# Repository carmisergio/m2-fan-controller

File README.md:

# M.2 fan controller
A simple PWM fan controller designed to fit in an E-Key M.2 slot normally designed for WiFi/Bluetooth cards.

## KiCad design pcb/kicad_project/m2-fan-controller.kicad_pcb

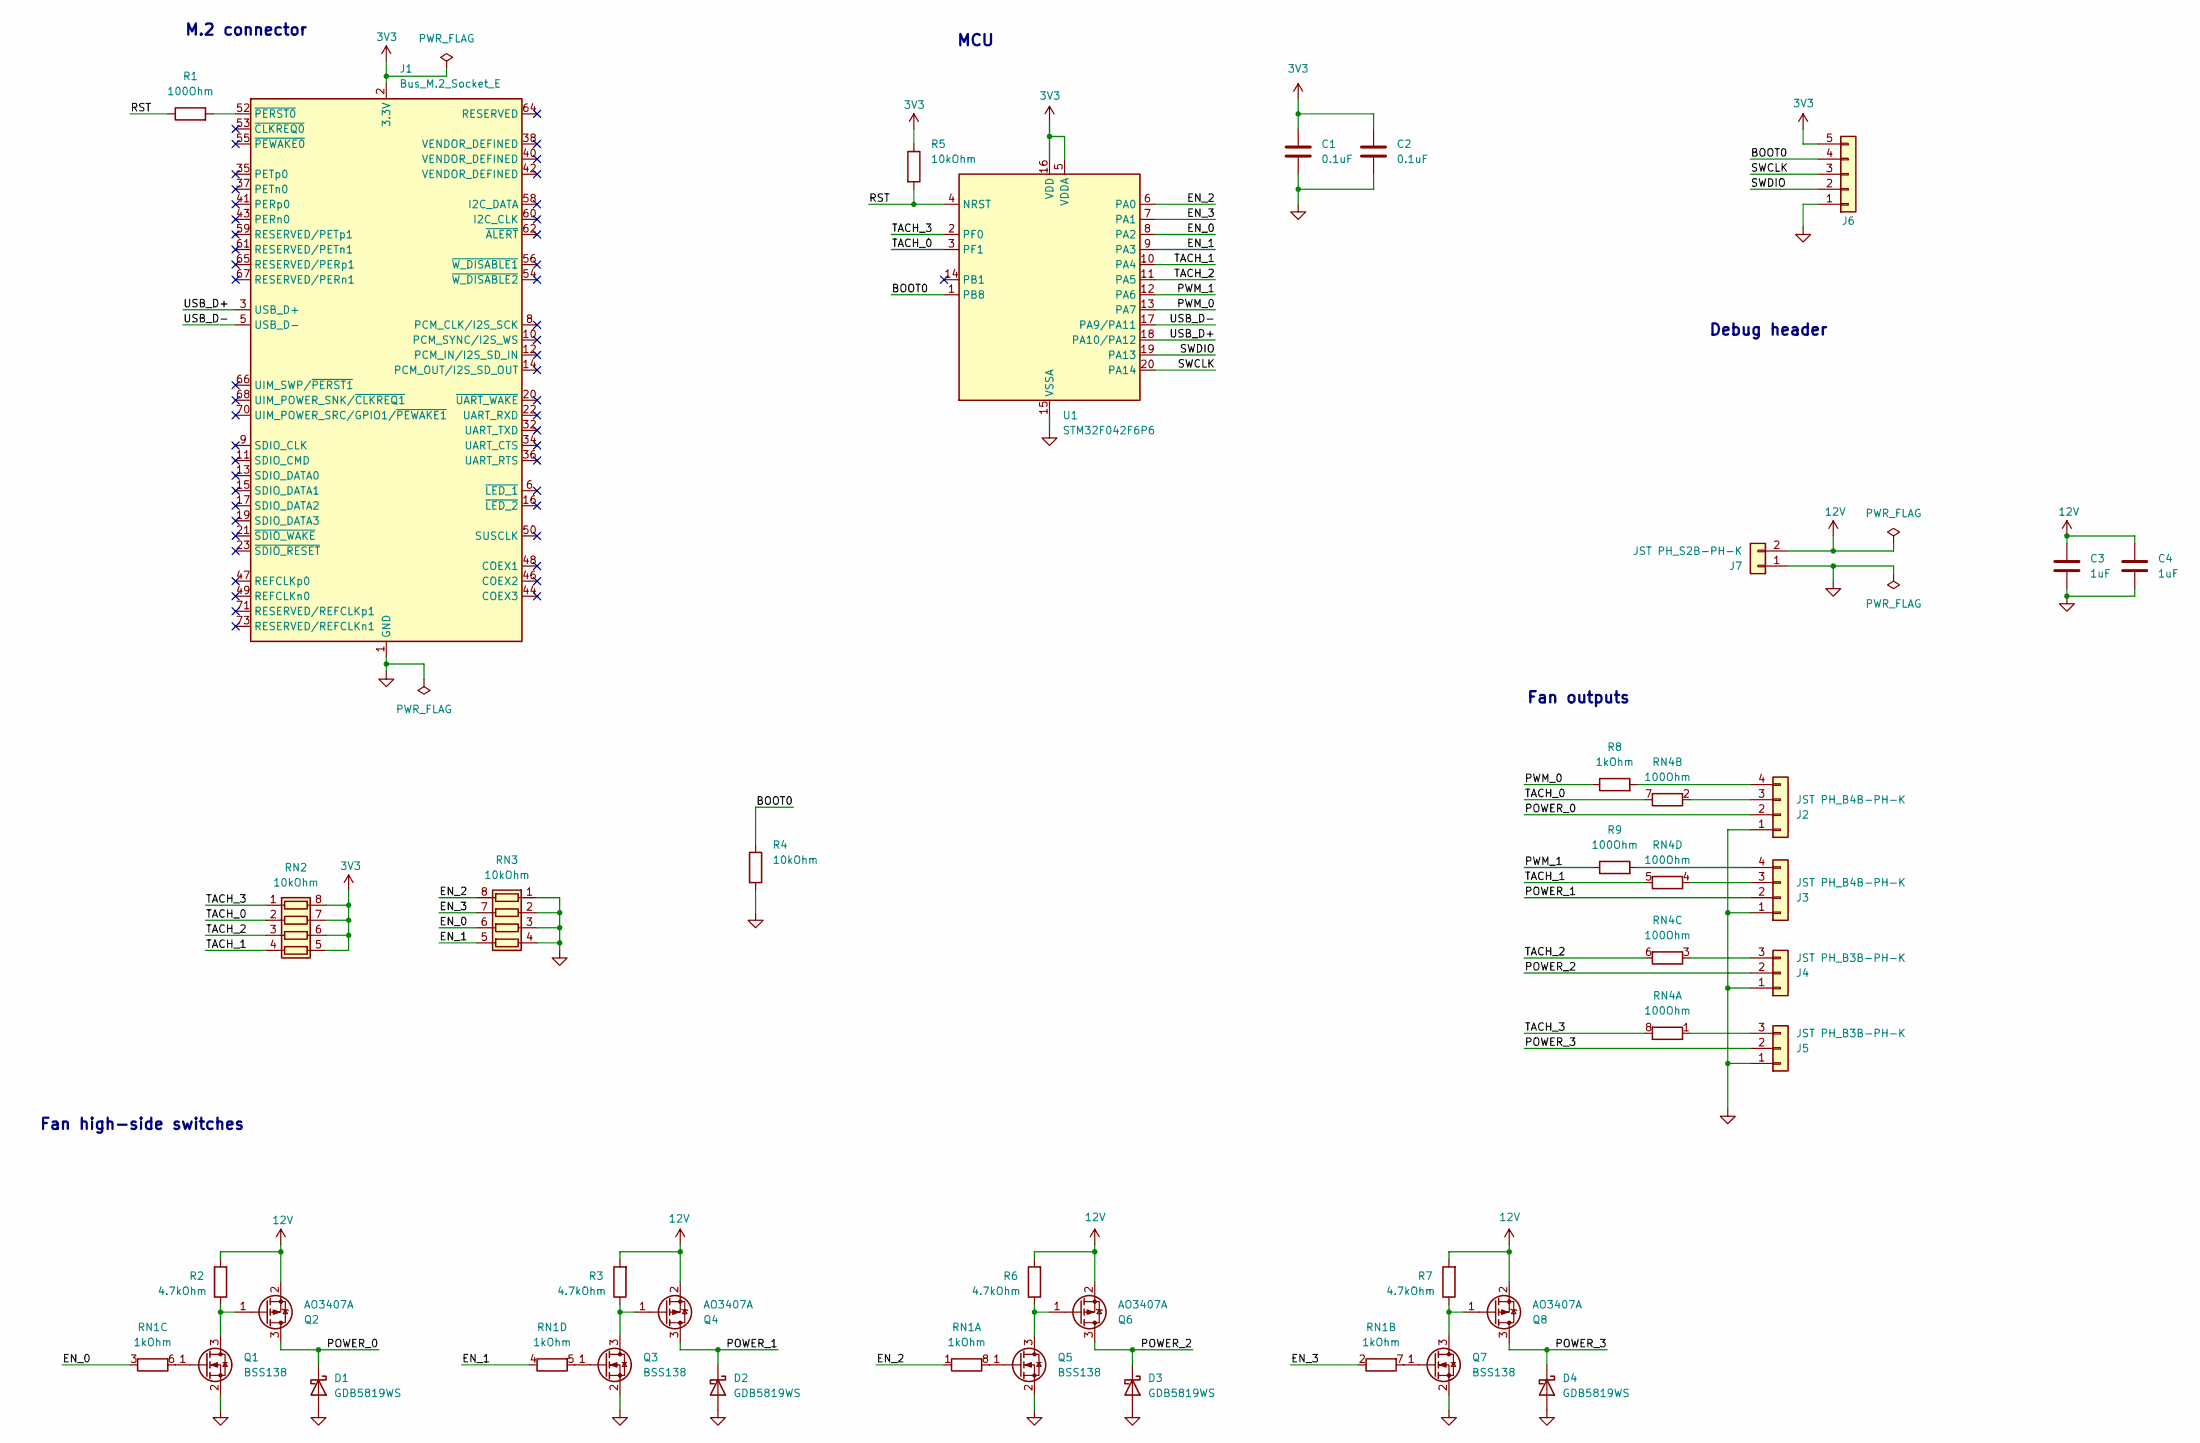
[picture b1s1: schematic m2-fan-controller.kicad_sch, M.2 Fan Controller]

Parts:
C1, C2: 0.1uF; C_0603_1608Metric_Pad1.08x0.95mm_HandSolder
C3, C4: 1uF; C_0805_2012Metric_Pad1.18x1.45mm_HandSolder
D1, D2, D3, D4: GDB5819WS; D_SOD-323_HandSoldering
J1: Bus_M.2_Socket_E; M.2_2230-xx-E
J2, J3: JST PH_B4B-PH-K; JST_PH_B4B-PH-K_1x04_P2.00mm_Vertical
J4, J5: JST PH_B3B-PH-K; JST_PH_B3B-PH-K_1x03_P2.00mm_Vertical
J6: Conn_02x02_Odd_Even; PinHeader_1x05_P1.27mm_Vertical
J7: JST PH_S2B-PH-K; JST_PH_B2B-PH-K_1x02_P2.00mm_Vertical
Q1, Q3, Q5, Q7: BSS138; SOT-23
Q2, Q4, Q6, Q8: AO3407A; SOT-23
R1, R9: 100Ohm; R_0603_1608Metric_Pad0.98x0.95mm_HandSolder
R2, R3, R6, R7: 4.7kOhm; R_0603_1608Metric_Pad0.98x0.95mm_HandSolder
R4, R5: 10kOhm; R_0603_1608Metric_Pad0.98x0.95mm_HandSolder
R8: 1kOhm; R_0603_1608Metric_Pad0.98x0.95mm_HandSolder
RN1: 1kOhm; R_Array_Convex_4x0603
RN2, RN3: 10kOhm; R_Array_Convex_4x0603
RN4: 100Ohm; R_Array_Convex_4x0603
U1: STM32F042F6P6; TSSOP-20_4.4x6.5mm_P0.65mm

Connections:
3V3: C1.1, C2.1, J1.2 (3.3V), J1.4 (3.3V), J1.72 (3.3V), J1.74 (3.3V), J6.5, R5.1, RN2.5 (R4.2), RN2.6 (R3.2), RN2.7 (R2.2), RN2.8 (R1.2), U1.5 (VDDA), U1.16 (VDD)
12V: C3.1, C4.1, J7.2, Q2.2 (S), Q4.2 (S), Q6.2 (S), Q8.2 (S), R2.2, R3.2, R6.2, R7.2
/BOOT0: J6.4, R4.1, U1.1 (PB8)
/EN_0: RN1.3 (R3.1), RN3.6 (R3.2), U1.8 (PA2)
/EN_1: RN1.4 (R4.1), RN3.5 (R4.2), U1.9 (PA3)
/EN_2: RN1.1 (R1.1), RN3.8 (R1.2), U1.6 (PA0)
/EN_3: RN1.2 (R2.1), RN3.7 (R2.2), U1.7 (PA1)
/POWER_0: D1.1 (K), J2.2, Q2.3 (D)
/POWER_1: D2.1 (K), J3.2, Q4.3 (D)
/POWER_2: D3.1 (K), J4.2, Q6.3 (D)
/POWER_3: D4.1 (K), J5.2, Q8.3 (D)
/PWM_0: R8.1, U1.13 (PA7)
/PWM_1: R9.1, U1.12 (PA6)
/RST: R1.1, R5.2, U1.4 (NRST)
/SWCLK: J6.3, U1.20 (PA14)
/SWDIO: J6.2, U1.19 (PA13)
/TACH_0: RN2.2 (R2.1), RN4.7 (R2.2), U1.3 (PF1)
/TACH_1: RN2.4 (R4.1), RN4.5 (R4.2), U1.10 (PA4)
/TACH_2: RN2.3 (R3.1), RN4.6 (R3.2), U1.11 (PA5)
/TACH_3: RN2.1 (R1.1), RN4.8 (R1.2), U1.2 (PF0)
/USB_D+: J1.3 (USB_D+), U1.18 (PA10/PA12)
/USB_D-: J1.5 (USB_D-), U1.17 (PA9/PA11)
GND: C1.2, C2.2, C3.2, C4.2, D1.2 (A), D2.2 (A), D3.2 (A), D4.2 (A), J1.1 (GND), J1.7 (GND), J1.18 (GND), J1.33 (GND), J1.39 (GND), J1.45 (GND), J1.51 (GND), J1.57 (GND), J1.63 (GND), J1.69 (GND), J1.75 (GND), J2.1, J3.1, J4.1, J5.1, J6.1, J7.1, Q1.2 (S), Q3.2 (S), Q5.2 (S), Q7.2 (S), R4.2, RN3.1 (R1.1), RN3.2 (R2.1), RN3.3 (R3.1), RN3.4 (R4.1), U1.15 (VSSA)
unnamed: J1.52 (~PERST0), R1.2
unnamed: J2.3, RN4.2 (R2.1)
unnamed: J2.4, R8.2
unnamed: J3.3, RN4.4 (R4.1)
unnamed: J3.4, R9.2
unnamed: J4.3, RN4.3 (R3.1)
unnamed: J5.3, RN4.1 (R1.1)
unnamed: Q1.3 (D), Q2.1 (G), R2.1
unnamed: Q1.1 (G), RN1.6 (R3.2)
unnamed: Q3.3 (D), Q4.1 (G), R3.1
unnamed: Q3.1 (G), RN1.5 (R4.2)
unnamed: Q5.3 (D), Q6.1 (G), R6.1
unnamed: Q5.1 (G), RN1.8 (R1.2)
unnamed: Q7.3 (D), Q8.1 (G), R7.1
unnamed: Q7.1 (G), RN1.7 (R2.2)

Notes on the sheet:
Fan outputs
M.2 connector
MCU
Fan high-side switches
Debug header

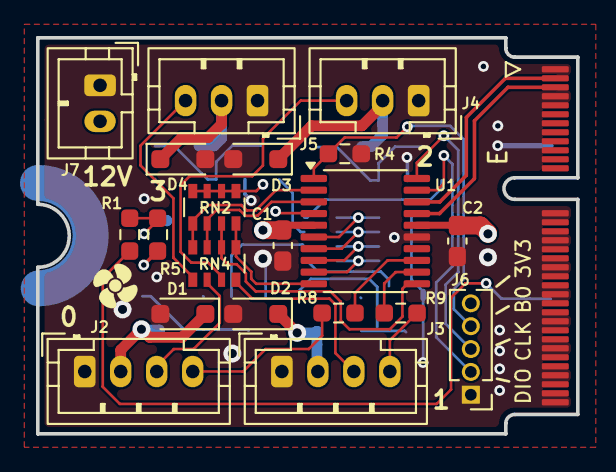
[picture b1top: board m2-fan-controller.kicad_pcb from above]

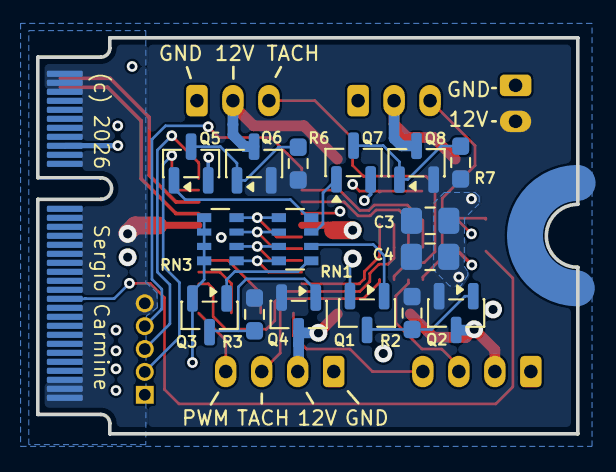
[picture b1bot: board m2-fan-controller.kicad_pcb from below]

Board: 4 copper layers, 30.0 x 22.0 mm, 37 parts (16 on the bottom side), 38 nets.

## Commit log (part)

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2026-02-10 pcb: initial project setup
2026-02-11 pcb: shcematics + initial component placement
2026-02-12 Hopefully final revision
2026-02-14 Add debug header
2026-02-14 Final revision
2026-02-15 Use 0603 components

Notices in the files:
pcb/kicad_project/m2-fan-controller.kicad_pcb:
(c) 2026 Sergio Carmine
